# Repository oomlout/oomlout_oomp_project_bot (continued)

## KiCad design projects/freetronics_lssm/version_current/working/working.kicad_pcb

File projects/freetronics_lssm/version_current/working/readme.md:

# LSSM by freetronics  
This is a harvested standardized copy of a project from github.  
The original project can be found at:  
https://github.com/freetronics/LSSM  
Please consult that link for additional, details, files, and license information.  
Note: It was auto harvested and if the original repo had more than one board file or anything out of the ordinary the files here are likely not representative.

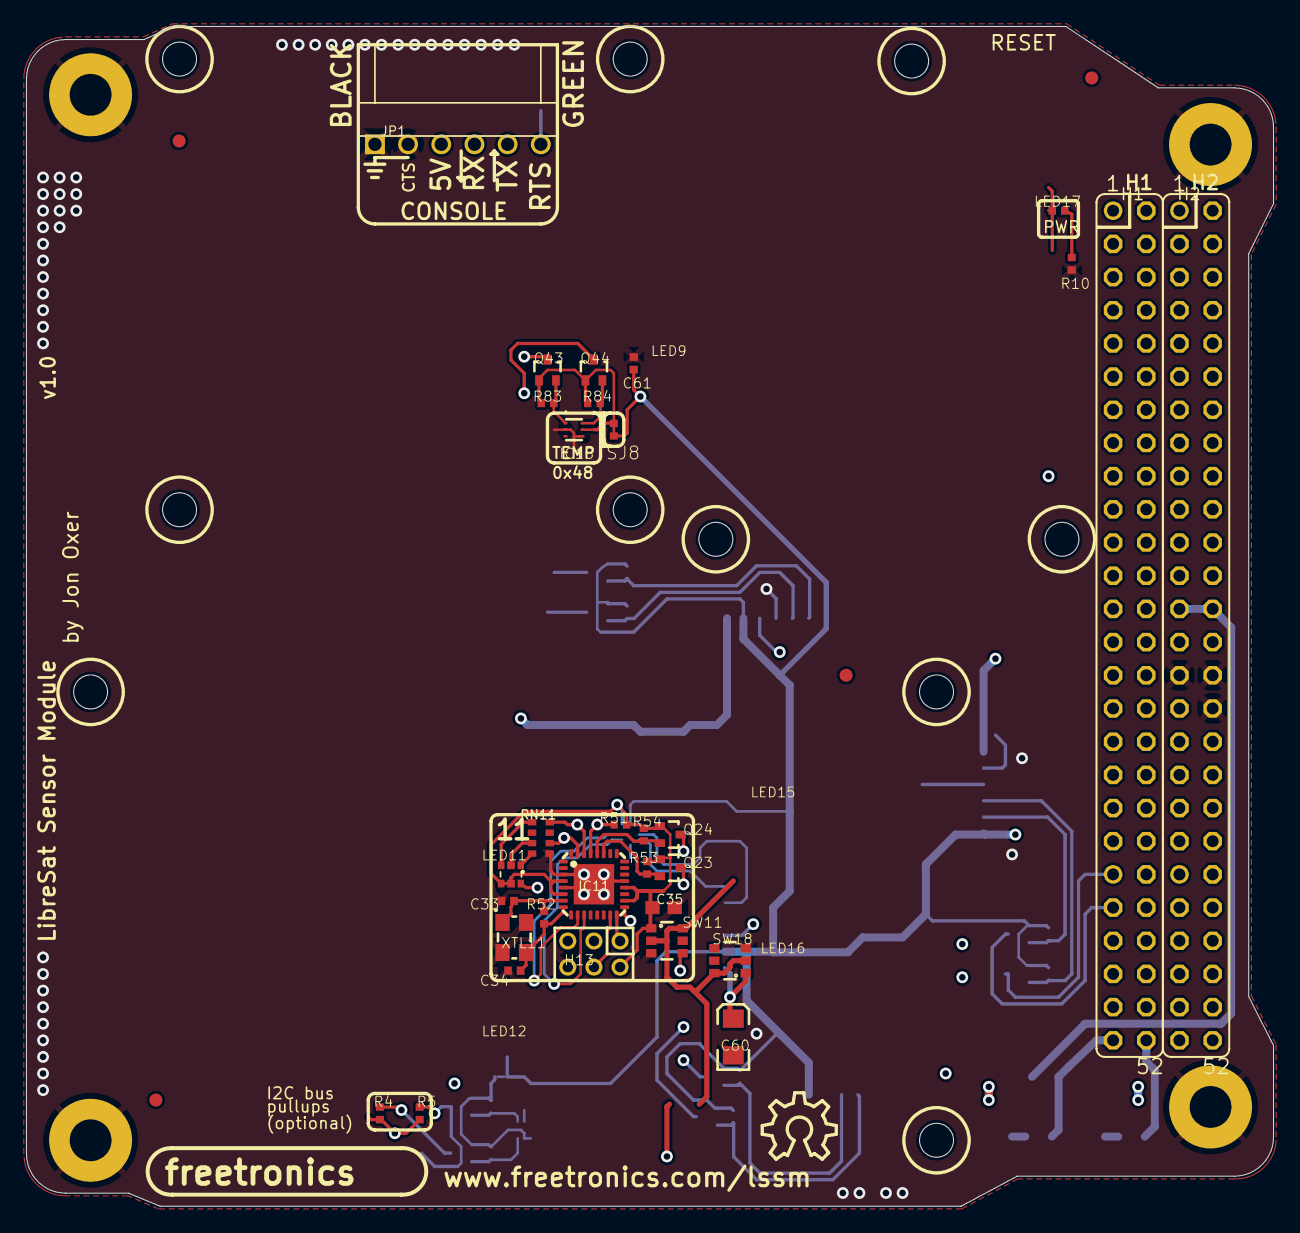
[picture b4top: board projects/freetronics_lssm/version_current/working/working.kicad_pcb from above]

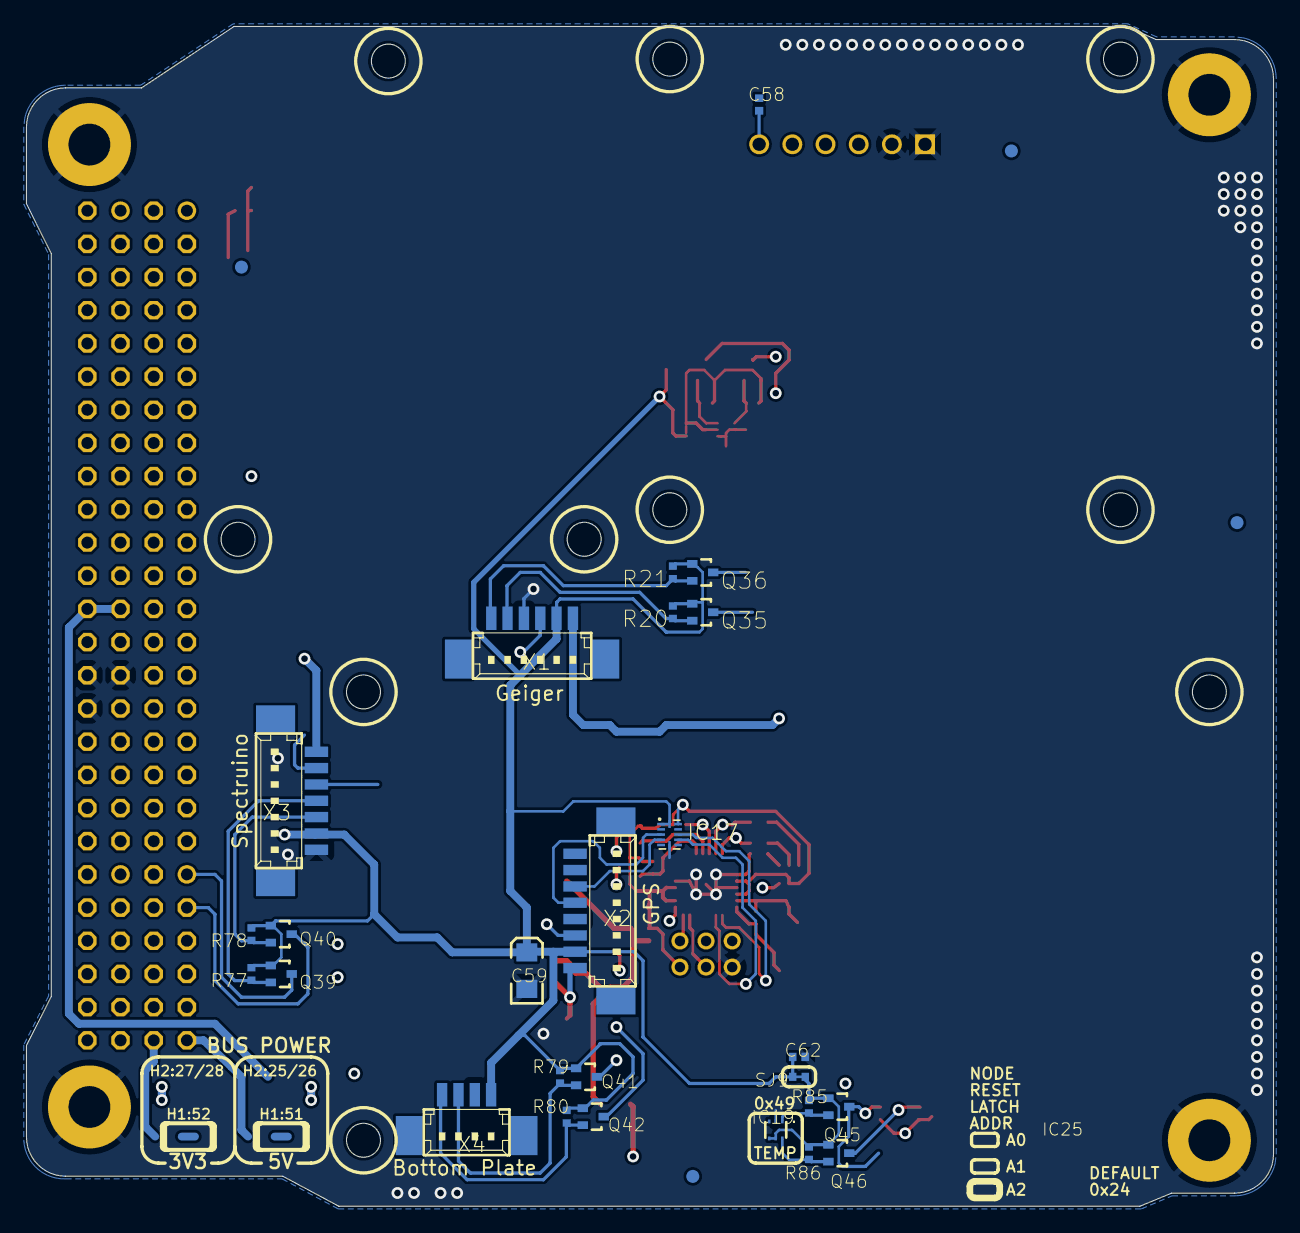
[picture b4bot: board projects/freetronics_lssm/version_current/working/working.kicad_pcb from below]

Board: 4 copper layers, 95.5 x 90.3 mm, 80 parts (30 on the bottom side), 42 nets.

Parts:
@HOLE0, @HOLE1, @HOLE2, @HOLE3, @HOLE4, @HOLE5, @HOLE6, @HOLE7, @HOLE8, @HOLE9: (no value)
C33, C34: 22pF 0402; 0402C
C35: 1uF 0603; C0603
C58, C61, C62: 100nF 0402; 0402C
C59, C60: 10uF 10V A TANT; EIA3216
FID1, FID2, FID3, FID4, FID5, FID6, FID7, FID8: FIDUCIAL1X2.5; FIDUCIAL-1X2.5
H1, H2: CUBESATBUSH; CUBESATBUS
H13: ICSP; M2X3-2MM
IC11: ATMEGA328P QFN32; MLF32
IC17: TXB0104; QFN-12
IC18, IC19: TMP102; SOT563
JP1: DEBUG; MOLEX-1X6-RA
LED11: FREETRONICS-MASTER-V1_RGBLEDSMT; FREETRONICS-MASTER-V1_19-337
LED17: BLUE 0402; LED-0402
MNT1, MNT2, MNT3, MNT4: HOLE3.2MM; HOLE32
Q23, Q24, Q35, Q36, Q39, Q40, Q41, Q42, Q43, Q44, Q45, Q46: RJU003N03 N-MOSFET; SOT32-3
R4, R5, R53, R54, R83, R84, R85, R86: 10K 0402; 0402
R10: 2K2 0402; 0402
R20, R21, R77, R78, R79, R80: 4K7 0402; 0402
R51: 22K 0402; 0402
R52: 1M 0402; 0402
RN11: 2K2; CAY16
SJ8, SJ9: SJC0402; 0402SJC
SW11, SW18: ADG801 SOT23-6; SOT23-6
U$33: OSHW_10X200_NOTEXT
X1: Geiger; 53398-06
X2: gps; 53398-08
X3: Spectruino; 53398-07
X4: Bottom Plate; 53398-04
XTL11: SMD3225-8MHZ 3.2 x 2.5mm crystal; CRYSTAL-SMD-3X2

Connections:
3.3V: C59.A, C61.1, C62.1, IC17.1, IC17.12, Q35.1, Q36.1, Q39.1, Q40.1, Q41.1, Q42.1, R20.2, R21.2, R77.2, R78.2, R79.2, R80.2, SJ8.1, SJ9.1, X1.5, X2.2, X3.6, X4.4
5V: LED17.A, R4.2, R5.2, SW11.2, SW11.6, SW18.2, SW18.6, X1.6, X3.1
+5V_SYS: H2.25, H2.26
BOTTOM_SCL: Q42.2, R80.1, X4.1
BOTTOM_SDA: Q41.2, R79.1, X4.2
GEIGER_SCL: Q36.2, R21.1, X1.1
GEIGER_SDA: Q35.2, R20.1, X1.2
GND: C33.1, C34.1, C35.2, C59.C, C60.C, C61.2, C62.2, H2.29, H2.30, H2.32, H13.6, IC11.3, IC11.5, IC11.21, IC11.TGND, IC17.6, IC18.2, IC18.4, IC19.2, JP1.1, JP1.2, MNT1.P$1, MNT2.P$1, MNT3.P$1, MNT4.P$1, R10.1, RN11.1, SW11.3, SW18.3, X1.3, X2.4, X3.7, X4.3, XTL11.2, XTL11.4
GPS_5V: C60.A, SW18.1, X2.1
N11_5V: C35.1, H13.2, IC11.4, IC11.6, IC11.18, IC11.20, IC17.11, LED11.5, LED11.6, Q23.1, Q24.1, R51.2, R53.2, R54.2, SW11.1
N11_A4_SDA: IC11.27, Q23.2, R53.1
N11_A5_SCL: IC11.28, Q24.2, R54.1
N11_D0_RX: IC11.30, RN11.4
N11_D1_TX: IC11.31, RN11.2
N11_D6: IC11.10, IC17.9
N11_D7: IC11.11, IC17.8
N11_D11_MOSI: H13.4, IC11.15
N11_D12_MISO: H13.1, IC11.16
N11_D13_SCK: H13.3, IC11.17, LED11.4
N11_RESET: H13.5, IC11.29, R51.1
unnamed: LED17.C, R10.2
unnamed: C34.2, IC11.8, R52.1, XTL11.3
unnamed: C33.2, IC11.7, R52.2, XTL11.1
unnamed: LED11.2, RN11.7
unnamed: LED11.1, RN11.8
unnamed: LED11.3, RN11.5
unnamed: IC18.1, Q43.2, R83.1
unnamed: IC18.6, Q44.2, R84.1
unnamed: IC19.6, Q46.2, R86.1
unnamed: IC19.1, Q45.2, R85.1
unnamed: IC18.5, Q43.1, Q44.1, R83.2, R84.2, SJ8.2
unnamed: IC19.4, IC19.5, Q45.1, Q46.1, R85.2, R86.2, SJ9.2
RTS: C58.1, JP1.6
RXD1: H1.36, JP1.4
RX_GPS: IC17.4, X2.6
SCL: H1.43, Q24.3, Q36.3, Q40.3, Q42.3, Q43.3, Q45.3, R5.1
SDA: H1.41, Q23.3, Q35.3, Q39.3, Q41.3, Q44.3, Q46.3, R4.1
SPEC_SCL: Q40.2, R78.1, X3.5
SPEC_SDA: Q39.2, R77.1, X3.4
TXD1: H1.34, JP1.5
TX_GPS: IC17.3, X2.5
VCC_SYS: H2.27, H2.28

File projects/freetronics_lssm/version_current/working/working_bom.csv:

"Id";"Designator";"Footprint";"Quantity";"Designation";"Supplier and ref";
1;"Q23,Q44,Q43,Q24,Q42,Q36,Q46,Q35,Q41,Q40,Q39,Q45";"SOT32-3";12;"RJU003N03 N-MOSFET";;;
2;"RN11";"CAY16";1;"2K2";;;
3;"MNT1,MNT2,MNT3,MNT4";"HOLE32";4;"HOLE3.2MM";;;
4;"@HOLE6,@HOLE5,@HOLE9,@HOLE4,@HOLE2,@HOLE3,@HOLE8,@HOLE7,@HOLE1,@HOLE0";"";10;"";;;
5;"R53,R5,R54,R84,R83,R4,R85,R86";"0402";8;"10K 0402";;;
6;"C60,C59";"EIA3216";2;"10uF 10V A TANT";;;
7;"LED11";"FREETRONICS-MASTER-V1_19-337";1;"FREETRONICS-MASTER-V1_RGBLEDSMT";;;
8;"R52";"0402";1;"1M 0402";;;
9;"C35";"C0603";1;"1uF 0603";;;
10;"IC18,IC19";"SOT563";2;"TMP102";;;
11;"LED17";"LED-0402";1;"BLUE 0402";;;
12;"FID2,FID4,FID1,FID3,FID8,FID5,FID7,FID6";"FIDUCIAL-1X2.5";8;"FIDUCIAL1X2.5";;;
13;"SW18,SW11";"SOT23-6";2;"ADG801 SOT23-6";;;
14;"C61,C62,C58";"0402C";3;"100nF 0402";;;
15;"H1,H2";"CUBESATBUS";2;"CUBESATBUSH";;;
16;"XTL11";"CRYSTAL-SMD-3X2";1;"SMD3225-8MHZ 3.2 x 2.5mm crystal";;;
17;"C34,C33";"0402C";2;"22pF 0402";;;
18;"R51";"0402";1;"22K 0402";;;
19;"H13";"M2X3-2MM";1;"ICSP";;;
20;"R10";"0402";1;"2K2 0402";;;
21;"SJ8,SJ9";"0402SJC";2;"SJC0402";;;
22;"JP1";"MOLEX-1X6-RA";1;"DEBUG";;;
23;"U$33";"OSHW_10X200_NOTEXT";1;"";;;
24;"IC11";"MLF32";1;"ATMEGA328P QFN32";;;
25;"R21,R80,R79,R78,R20,R77";"0402";6;"4K7 0402";;;
26;"X1";"53398-06";1;"Geiger";;;
27;"X4";"53398-04";1;"Bottom Plate";;;
28;"IC17";"QFN-12";1;"TXB0104";;;
29;"X2";"53398-08";1;"gps";;;
30;"X3";"53398-07";1;"Spectruino";;;

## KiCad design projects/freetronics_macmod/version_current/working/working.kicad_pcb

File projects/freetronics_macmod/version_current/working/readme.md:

# MACMOD by freetronics  
This is a harvested standardized copy of a project from github.  
The original project can be found at:  
https://github.com/freetronics/MACMOD  
Please consult that link for additional, details, files, and license information.  
Note: It was auto harvested and if the original repo had more than one board file or anything out of the ordinary the files here are likely not representative.

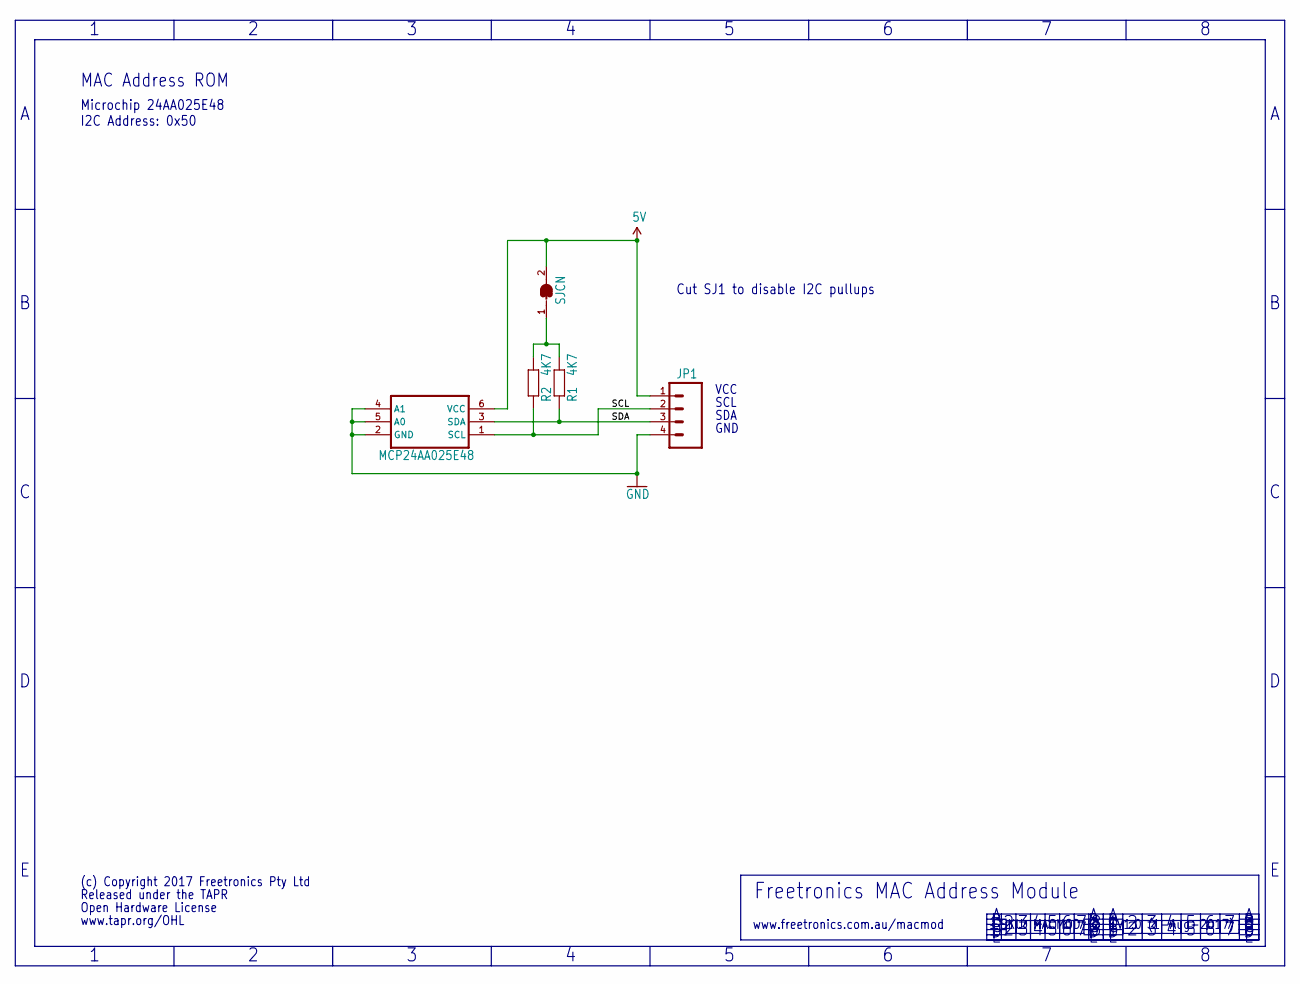
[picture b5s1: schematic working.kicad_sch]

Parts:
IC1: MCP24AA025E48; SOT23-6
JP1: M04PTH; 1X04
R1, R2: 4K7; 0603
SJ1: SJCN; SJC

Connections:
5V: IC1.6 (VCC), JP1.1, SJ1.2
GND: IC1.2 (GND), IC1.4 (A1), IC1.5 (A0), JP1.4
unnamed: R1.2, R2.2, SJ1.1
SCL: IC1.1 (SCL), JP1.2, R2.1
SDA: IC1.3 (SDA), JP1.3, R1.1

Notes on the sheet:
MAC Address ROM
Microchip 24AA025E48 I2C Address: 0x50
Cut SJ1 to disable I2C pullups
VCC
(c) Copyright 2017 Freetronics Pty Ltd
Open Hardware License
SCL
www.freetronics.com.au/macmod
V1.0 (1-Aug-2017)
GND
SKU: MACMOD
SDA
Released under the TAPR
www.tapr.org/OHL
Freetronics MAC Address Module

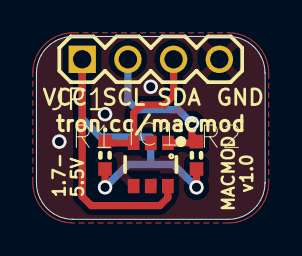
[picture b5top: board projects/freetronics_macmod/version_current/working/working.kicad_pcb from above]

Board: 2 copper layers, 12.7 x 10.2 mm, 5 parts (1 on the bottom side), 5 nets.

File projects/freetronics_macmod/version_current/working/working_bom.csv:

"Id";"Designator";"Footprint";"Quantity";"Designation";"Supplier and ref";
1;"JP1";"1X04";1;"";;;
2;"R1,R2";"0603";2;"4K7";;;
3;"IC1";"SOT23-6";1;"MCP24AA025E48";;;
4;"SJ1";"SJC";1;"SJCN";;;

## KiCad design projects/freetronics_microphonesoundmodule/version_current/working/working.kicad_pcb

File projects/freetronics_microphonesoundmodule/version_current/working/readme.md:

# MicrophoneSoundModule by freetronics  
This is a harvested standardized copy of a project from github.  
The original project can be found at:  
https://github.com/freetronics/MicrophoneSoundModule  
Please consult that link for additional, details, files, and license information.  
Note: It was auto harvested and if the original repo had more than one board file or anything out of the ordinary the files here are likely not representative.

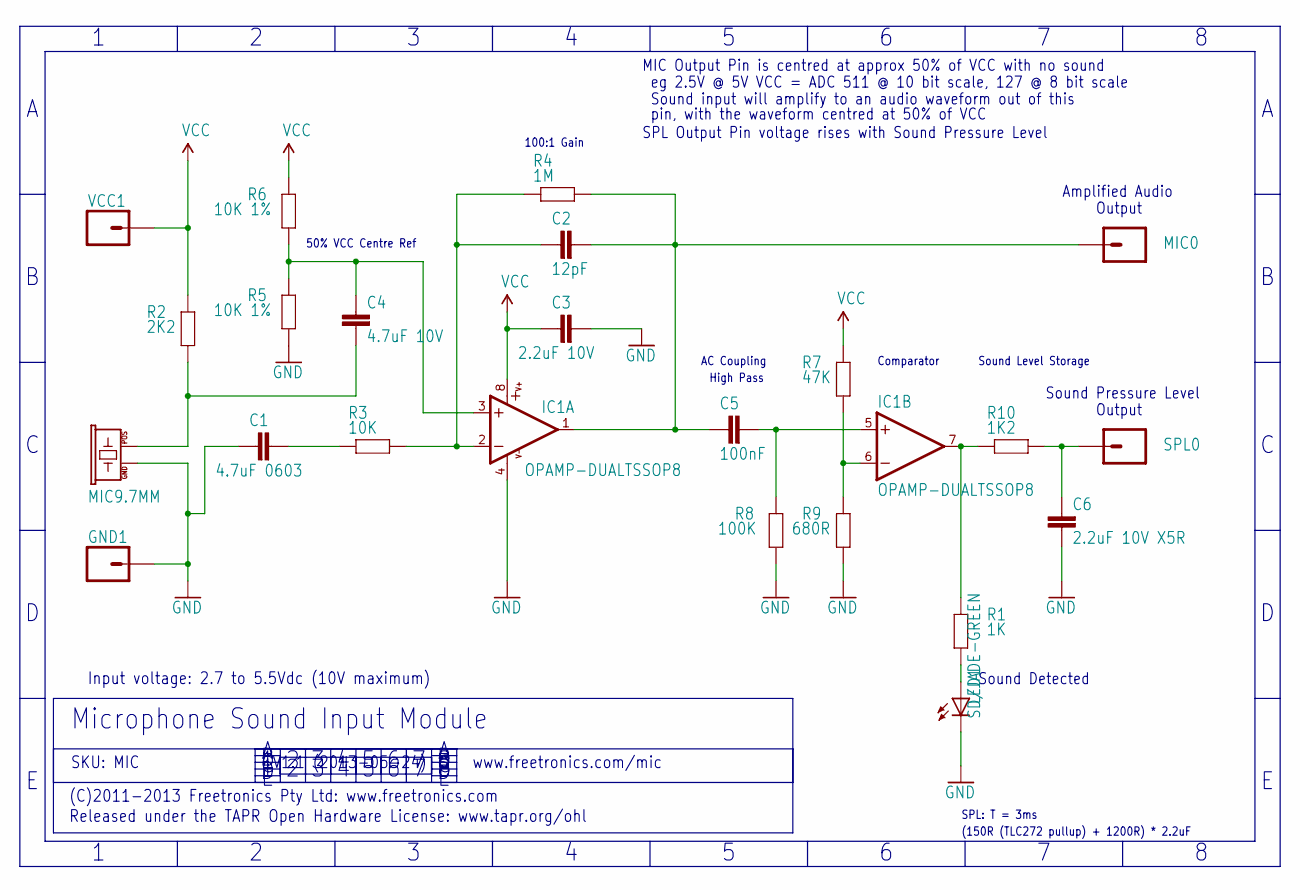
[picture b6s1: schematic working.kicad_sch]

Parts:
C1: 4.7uF 0603; 0603
C2: 12pF; 0603
C3: 2.2uF 10V; 0603
C4: 4.7uF 10V; 0603
C5: 100nF; 0603
C6: 2.2uF 10V X5R; 0603
GND1: M01PTH; 1X01
IC1: OPAMP-DUALTSSOP8; TSSOP8
LED1: SD/JADE-GREEN; LED-0603
MIC0: M01PTH; 1X01
MIC1: MIC9.7MM; MIC-9.7MM
R1: 1K; 0603
R2: 2K2; 0603
R3: 10K; 0603
R4: 1M; 0603
R5, R6: 10K 1%; 0603
R7: 47K; 0603
R8: 100K; 0603
R9: 680R; 0603
R10: 1K2; 0603
SPL0: M01PTH; 1X01
VCC1: M01PTH; 1X01

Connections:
GND: C1.1, C3.2, C6.1, GND1.1, IC1.4 (V-), LED1.C, MIC1.GND, R5.1, R8.1, R9.1
unnamed: LED1.A, R1.1
unnamed: C4.1, MIC1.POS, R2.1
unnamed: C1.2, R3.2
unnamed: C2.1, IC1.2 (-IN), R3.1, R4.2
unnamed: C2.2, C5.1, IC1.1 (OUT), MIC0.1, R4.1
unnamed: C5.2, IC1.5 (+IN), R8.2
unnamed: C4.2, IC1.3 (+IN), R5.2, R6.1
unnamed: C6.2, R10.1, SPL0.1
unnamed: IC1.6 (-IN), R7.1, R9.2
unnamed: IC1.7 (OUT), R1.2, R10.2
VCC: C3.1, IC1.8 (V+), R2.2, R6.2, R7.2, VCC1.1

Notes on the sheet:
SPL Output Pin voltage rises with Sound Pressure Level
V1.1 (2013-05-24)
Comparator
pin, with the waveform centred at 50% of VCC
MIC Output Pin is centred at approx 50% of VCC with no sound
Sound Level Storage
Released under the TAPR Open Hardware License: www.tapr.org/ohl
eg 2.5V @ 5V VCC = ADC 511 @ 10 bit scale, 127 @ 8 bit scale
AC Coupling
Input voltage: 2.7 to 5.5Vdc (10V maximum)
(C)2011-2013 Freetronics Pty Ltd: www.freetronics.com
Output
www.freetronics.com/mic
Sound Detected
(150R (TLC272 pullup) + 1200R) * 2.2uF
Sound input will amplify to an audio waveform out of this
SPL: T = 3ms
50% VCC Centre Ref
SKU: MIC
Amplified Audio
High Pass
Sound Pressure Level
Microphone Sound Input Module
100:1 Gain

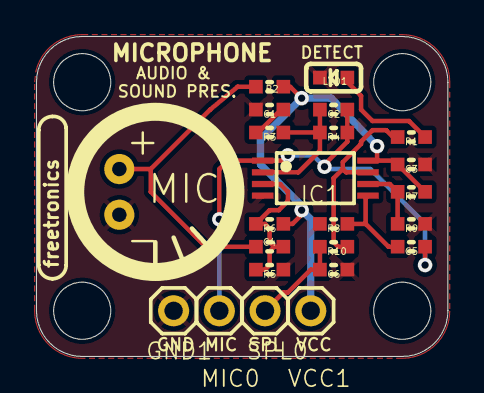
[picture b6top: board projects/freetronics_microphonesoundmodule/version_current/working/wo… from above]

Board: 2 copper layers, 22.9 x 17.8 mm, 27 parts (0 on the bottom side), 12 nets.

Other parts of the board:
@HOLE0, @HOLE1, @HOLE2, @HOLE3: (no value)

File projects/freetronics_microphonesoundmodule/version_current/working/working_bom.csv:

"Id";"Designator";"Footprint";"Quantity";"Designation";"Supplier and ref";
1;"@HOLE1,@HOLE0,@HOLE2,@HOLE3";"";4;"";;;
2;"C5";"0603";1;"100nF";;;
3;"C2";"0603";1;"12pF";;;
4;"R4";"0603";1;"1M";;;
5;"C1";"0603";1;"4.7uF 0603";;;
6;"C3";"0603";1;"2.2uF 10V";;;
7;"MIC1";"MIC-9.7MM";1;"MIC9.7MM";;;
8;"IC1";"TSSOP8";1;"TLC272 TSSOP8";;;
9;"LED1";"LED-0603";1;"SD/JADE-GREEN";;;
10;"R3";"0603";1;"10K";;;
11;"C6";"0603";1;"2.2uF 10V X5R";;;
12;"R1";"0603";1;"1K";;;
13;"R5,R6";"0603";2;"10K 1%";;;
14;"MIC0,SPL0,VCC1,GND1";"1X01";4;"M01PTH";;;
15;"R8";"0603";1;"100K";;;
16;"R9";"0603";1;"680R";;;
17;"R2";"0603";1;"2K2";;;
18;"C4";"0603";1;"4.7uF 10V";;;
19;"R10";"0603";1;"1K2";;;
20;"R7";"0603";1;"47K";;;

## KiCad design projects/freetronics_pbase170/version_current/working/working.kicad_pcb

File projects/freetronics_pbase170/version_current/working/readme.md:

# PBASE170 by freetronics  
This is a harvested standardized copy of a project from github.  
The original project can be found at:  
https://github.com/freetronics/PBASE170  
Please consult that link for additional, details, files, and license information.  
Note: It was auto harvested and if the original repo had more than one board file or anything out of the ordinary the files here are likely not representative.

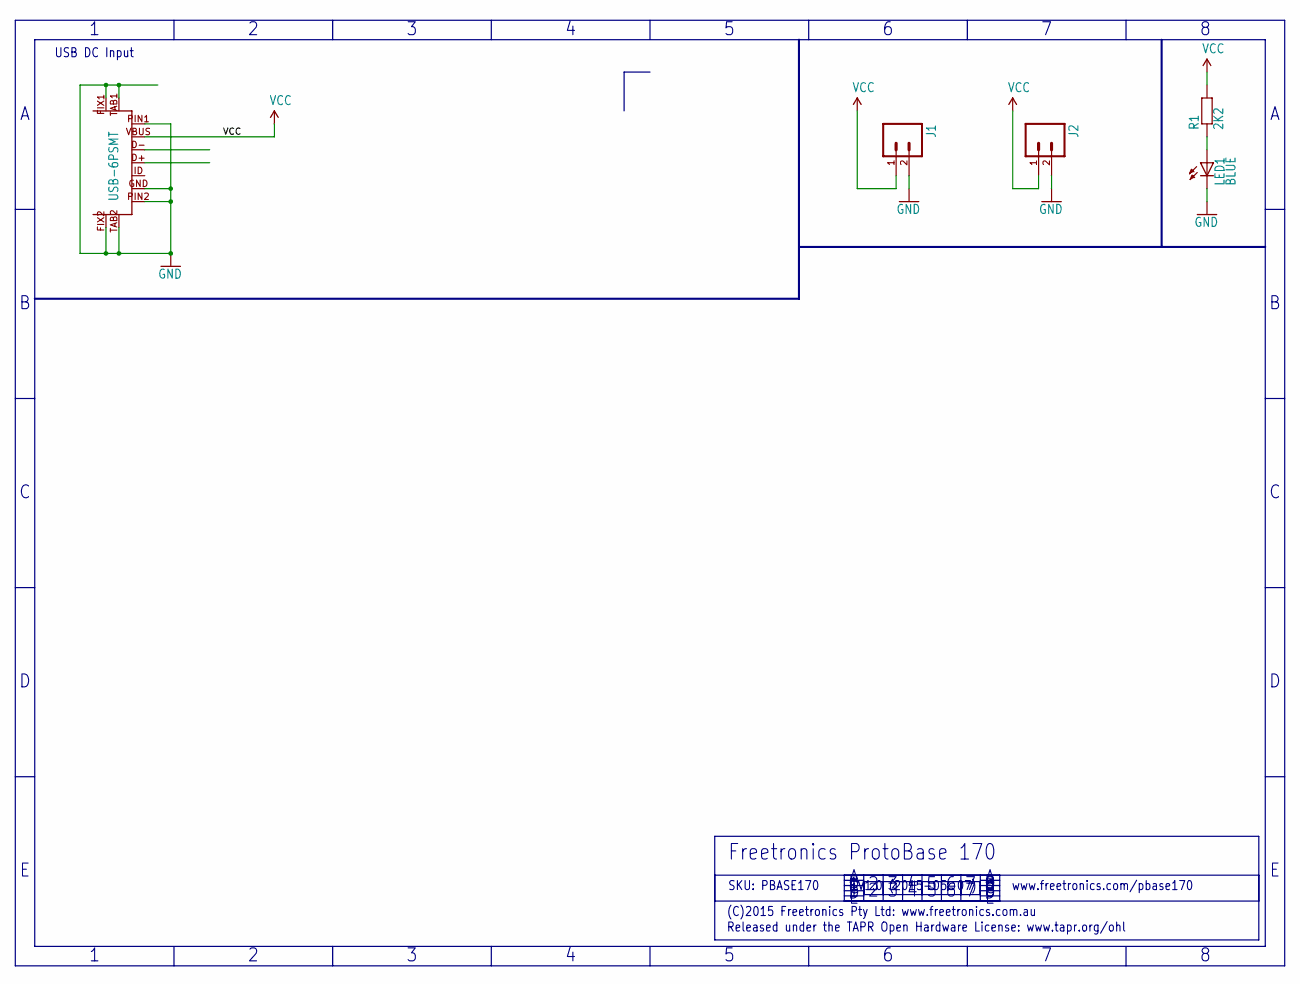
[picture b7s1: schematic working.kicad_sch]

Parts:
J1, J2: M02PTH; 1X02
LED1: BLUE; LED-0603
P1: USB-6PSMT; USB-MICROB-MB05PMXX
R1: 2K2; 0603

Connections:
GND: J1.2, J2.2, LED1.C, P1.FIX1, P1.FIX2, P1.GND, P1.PIN1, P1.PIN2, P1.TAB1, P1.TAB2
unnamed: LED1.A, R1.1
VCC: J1.1, J2.1, P1.VBUS, R1.2

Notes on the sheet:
www.freetronics.com/pbase170
Freetronics ProtoBase 170
Released under the TAPR Open Hardware License: www.tapr.org/ohl
V1.0 (2015-05-07)
USB DC Input
(C)2015 Freetronics Pty Ltd: www.freetronics.com.au
SKU: PBASE170

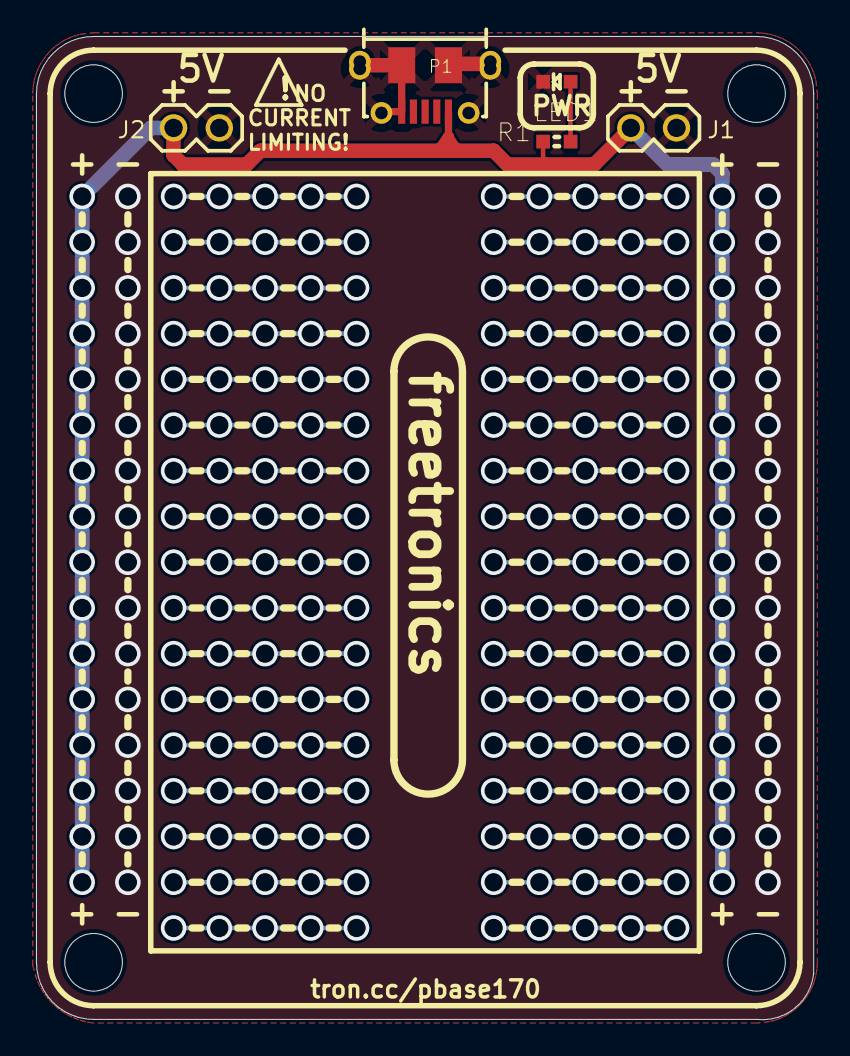
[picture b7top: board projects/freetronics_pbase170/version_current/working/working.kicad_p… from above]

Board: 2 copper layers, 43.2 x 54.6 mm, 9 parts (0 on the bottom side), 3 nets.

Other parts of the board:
@HOLE0, @HOLE1, @HOLE2, @HOLE3: (no value)

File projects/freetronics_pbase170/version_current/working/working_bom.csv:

"Id";"Designator";"Footprint";"Quantity";"Designation";"Supplier and ref";
1;"LED1";"LED-0603";1;"BLUE";;;
2;"@HOLE1,@HOLE0,@HOLE3,@HOLE2";"";4;"";;;
3;"R1";"0603";1;"2K2";;;
4;"J2,J1";"1X02";2;"";;;
5;"P1";"USB-MICROB-MB05PMXX";1;"USB-6PSMT";;;
